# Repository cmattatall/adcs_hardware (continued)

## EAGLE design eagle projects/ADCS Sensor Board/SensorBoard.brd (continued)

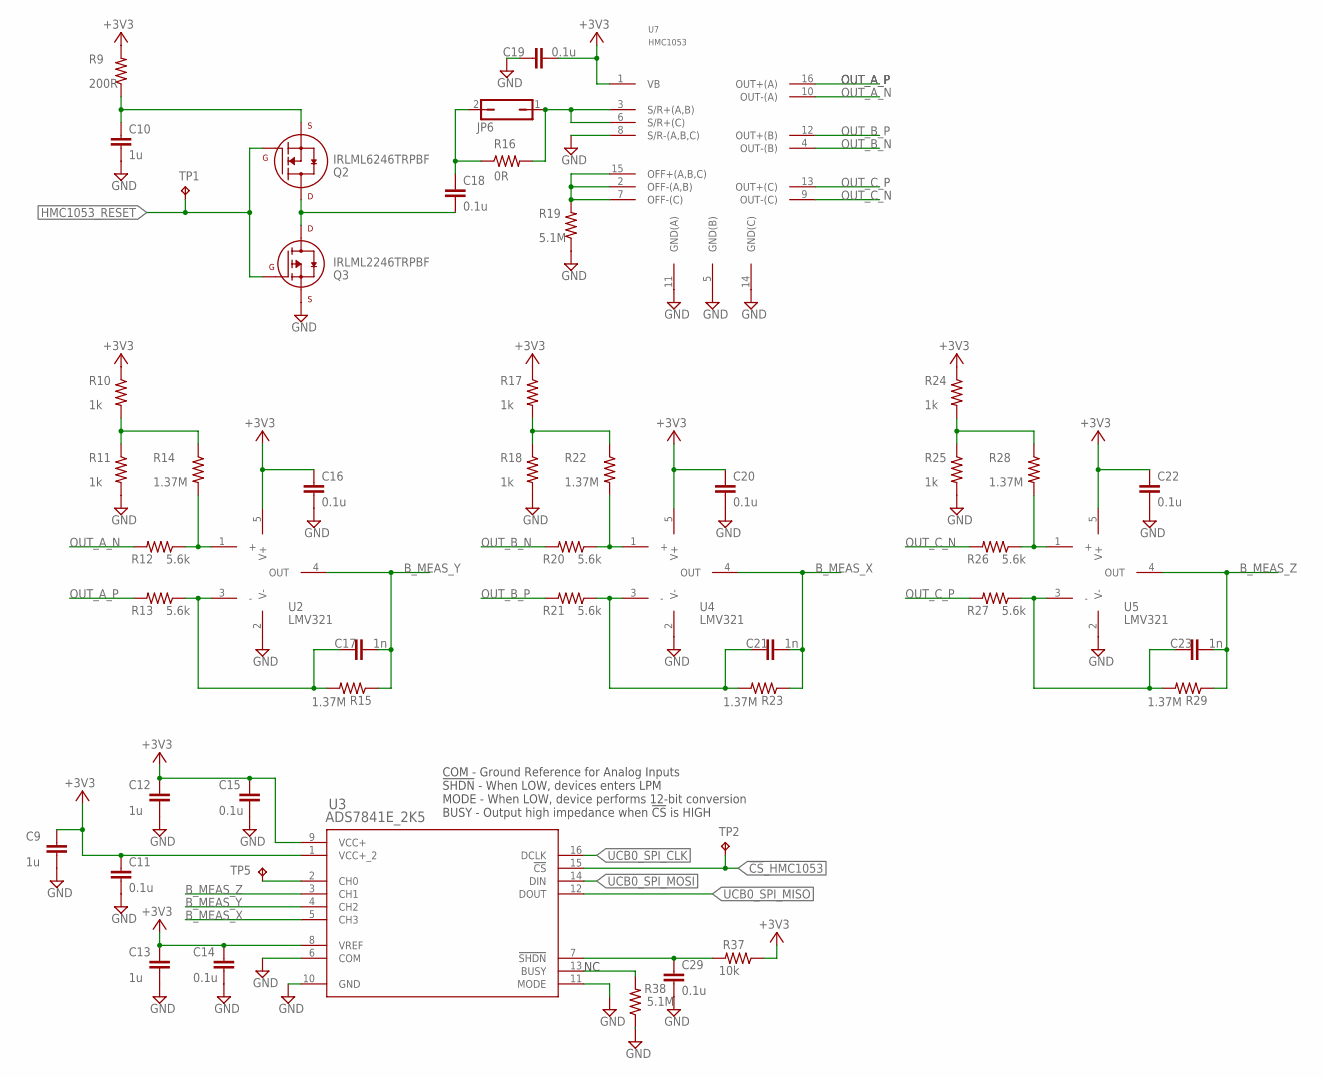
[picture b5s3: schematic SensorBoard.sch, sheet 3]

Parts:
C9, C12, C13: 1u; C0805
C10: 1u; C0603
C11, C14, C15, C16, C19, C20, C22, C29: 0.1u; C0603
C17, C21, C23: 1n; C0805
C18: 0.1u; C1206
JP6: JP1Q_; 1X02
Q2: IRLML6246TRPBF; SOT23-3P95_237X112L25X40N_MICRO3
Q3: IRLML2246TRPBF; SOT23-3P95_237X112L25X40N_MICRO3
R9: 200R; R0805
R10, R11, R17, R18, R24, R25: 1k; R0805
R12, R13, R20, R21, R26, R27: 5.6k; R0805
R14, R15, R22, R23, R28, R29: 1.37M; R0805
R16: 0R; R0805
R19: 5.1M; R0805
R37: 10k; R0805
R38: 5.1M; R0402
TP1, TP2, TP5: TESTPOINT; TP_P76H50
U2, U4, U5: LMV321; SC70-5P65_210X110L36X22N
U3: ADS7841E_2K5; DBQ16
U7: HMC1053; LCCS16P127_736X736X279L127X50N

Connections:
!CS!_HMC1053: TP2.1, U3.15 (!CS); also elsewhere on the board
+3V3: C9.1, C11.1, C12.1, C13.1, C14.1, C15.1, C16.1, C19.1, C20.1, C22.1, R9.2, R10.1, R17.1, R24.1, R37.1, U2.5 (V+), U3.1 (VCC+_2), U3.8 (VREF), U3.9 (VCC+), U4.5 (V+), U5.5 (V+), U7.1 (VB); also elsewhere on the board
B_MEAS_X: C21.2, R23.1, U3.5 (CH3), U4.4 (OUT)
B_MEAS_Y: C17.2, R15.1, U2.4 (OUT), U3.4 (CH2)
B_MEAS_Z: C23.2, R29.1, U3.3 (CH1), U5.4 (OUT)
GND: C9.2, C10.1, C11.2, C12.2, C13.2, C14.2, C15.2, C16.2, C19.2, C20.2, C22.2, C29.2, Q3.2 (S), R11.2, R18.2, R19.1, R25.2, R38.1, U2.2 (V-), U3.6 (COM), U3.10 (GND), U3.11 (MODE), U4.2 (V-), U5.2 (V-), U7.5 (GND(B)), U7.8 (S/R-(A,B,C)), U7.11 (GND(A)), U7.14 (GND(C)); also elsewhere on the board
HMC1053_RESET: Q2.1 (G), Q3.1 (G), TP1.1; also elsewhere on the board
unnamed: C18.1, Q2.3 (D), Q3.3 (D)
unnamed: R10.2, R11.1, R14.1
unnamed: C17.1, R13.1, R15.2, U2.3 (-)
unnamed: R12.1, R14.2, U2.1 (+)
unnamed: TP5.1, U3.2 (CH0)
unnamed: R38.2, U3.13 (BUSY)
unnamed: C29.1, R37.2, U3.7 (!SHDN)
unnamed: C18.2, JP6.2, R16.1
unnamed: R19.2, U7.2 (OFF-(A,B)), U7.7 (OFF-(C)), U7.15 (OFF+(A,B,C))
unnamed: JP6.1, R16.2, U7.3 (S/R+(A,B)), U7.6 (S/R+(C))
unnamed: C10.2, Q2.2 (S), R9.1
unnamed: R17.2, R18.1, R22.1
unnamed: C21.1, R21.1, R23.2, U4.3 (-)
unnamed: R20.1, R22.2, U4.1 (+)
unnamed: R24.2, R25.1, R28.1
unnamed: C23.1, R27.1, R29.2, U5.3 (-)
unnamed: R26.1, R28.2, U5.1 (+)
OUT_A_N: R12.2, U7.10 (OUT-(A))
OUT_A_P: R13.2, U7.16 (OUT+(A))
OUT_B_N: R20.2, U7.4 (OUT-(B))
OUT_B_P: R21.2, U7.12 (OUT+(B))
OUT_C_N: R26.2, U7.9 (OUT-(C))
OUT_C_P: R27.2, U7.13 (OUT+(C))
UCB0_SPI_CLK: U3.16 (DCLK); also elsewhere on the board
UCB0_SPI_MISO: U3.12 (DOUT); also elsewhere on the board
UCB0_SPI_MOSI: U3.14 (DIN); also elsewhere on the board

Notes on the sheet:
COM - Ground Reference for Analog Inputs !SHDN! - When LOW, devices enters LPM MODE - When LOW, device performs 12-bit conversion BUSY - Output high impedance when !CS! is HIGH

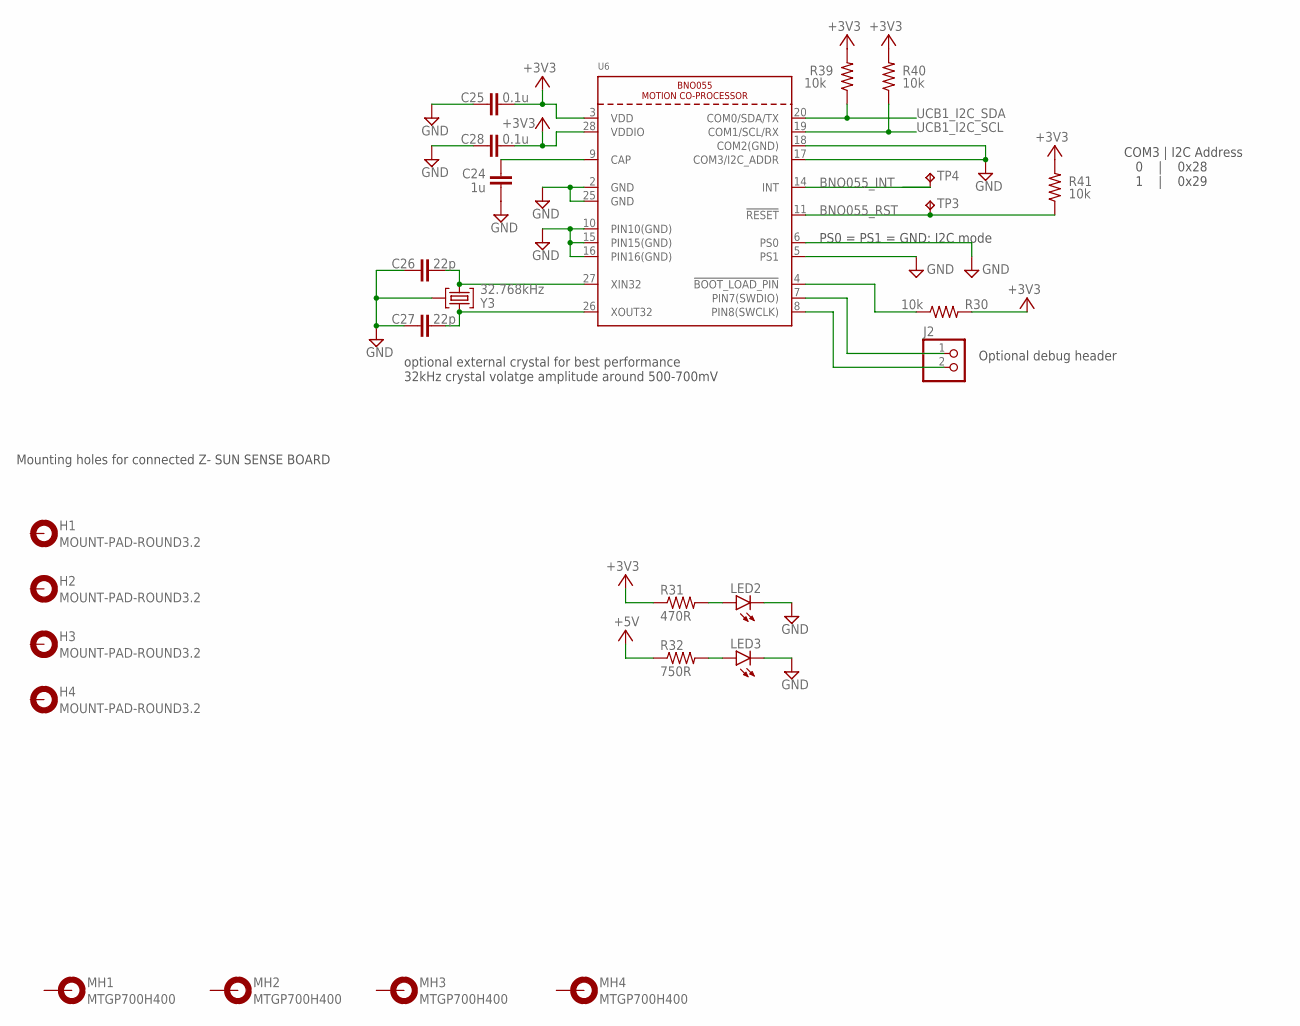
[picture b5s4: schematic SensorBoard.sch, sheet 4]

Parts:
C24: 1u; C0402
C25, C28: 0.1u; C0402
C26, C27: 22p; C0402
H1, H2, H3, H4: MOUNT-PAD-ROUND3.2; 3,2-PAD
J2: HDR_1X2_; 1X02
LED2, LED3: LEDCHIP-LED0603; CHIP-LED0603
MH1, MH2, MH3, MH4: MTGP700H400
R30, R39, R40, R41: 10k; R0402
R31: 470R; R0603
R32: 750R; R0603
TP3, TP4: TESTPOINT; TP_P76H50
U6: BNO055
Y3: 32.768kHz; MS3V-T1R

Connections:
+3V3: C25.2, C28.2, R30.2, R31.1, R39.2, R40.2, R41.2, U6.3 (VDD), U6.28 (VDDIO); also elsewhere on the board
+5V: R32.1; also elsewhere on the board
BNO055_INT: TP4.1, U6.14 (INT)
BNO055_RST: R41.1, TP3.1, U6.11 (!RESET)
GND: C24.1, C25.1, C26.1, C27.1, C28.1, LED2.C, LED3.C, U6.2 (GND), U6.5 (PS1), U6.6 (PS0), U6.10 (PIN10(GND)), U6.15 (PIN15(GND)), U6.16 (PIN16(GND)), U6.17 (COM3/I2C_ADDR), U6.18 (COM2(GND)), U6.25 (GND), Y3.P3 (GND); also elsewhere on the board
unnamed: LED2.A, R31.2
unnamed: LED3.A, R32.2
unnamed: R30.1, U6.4 (!BOOT_LOAD_PIN)
unnamed: C24.2, U6.9 (CAP)
unnamed: C26.2, U6.27 (XIN32), Y3.P1 (1)
unnamed: C27.2, U6.26 (XOUT32), Y3.P2 (2)
unnamed: J2.1, U6.7 (PIN7(SWDIO))
unnamed: J2.2, U6.8 (PIN8(SWCLK))
UCB1_I2C_SCL: R40.1, U6.19 (COM1/SCL/RX); also elsewhere on the board
UCB1_I2C_SDA: R39.1, U6.20 (COM0/SDA/TX); also elsewhere on the board

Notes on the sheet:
optional external crystal for best performance 32kHz crystal volatge amplitude around 500-700mV
Optional debug header
PS0 = PS1 = GND: I2C mode
COM3 | I2C Address 0 | 0x28 1 | 0x29
Mounting holes for connected Z- SUN SENSE BOARD

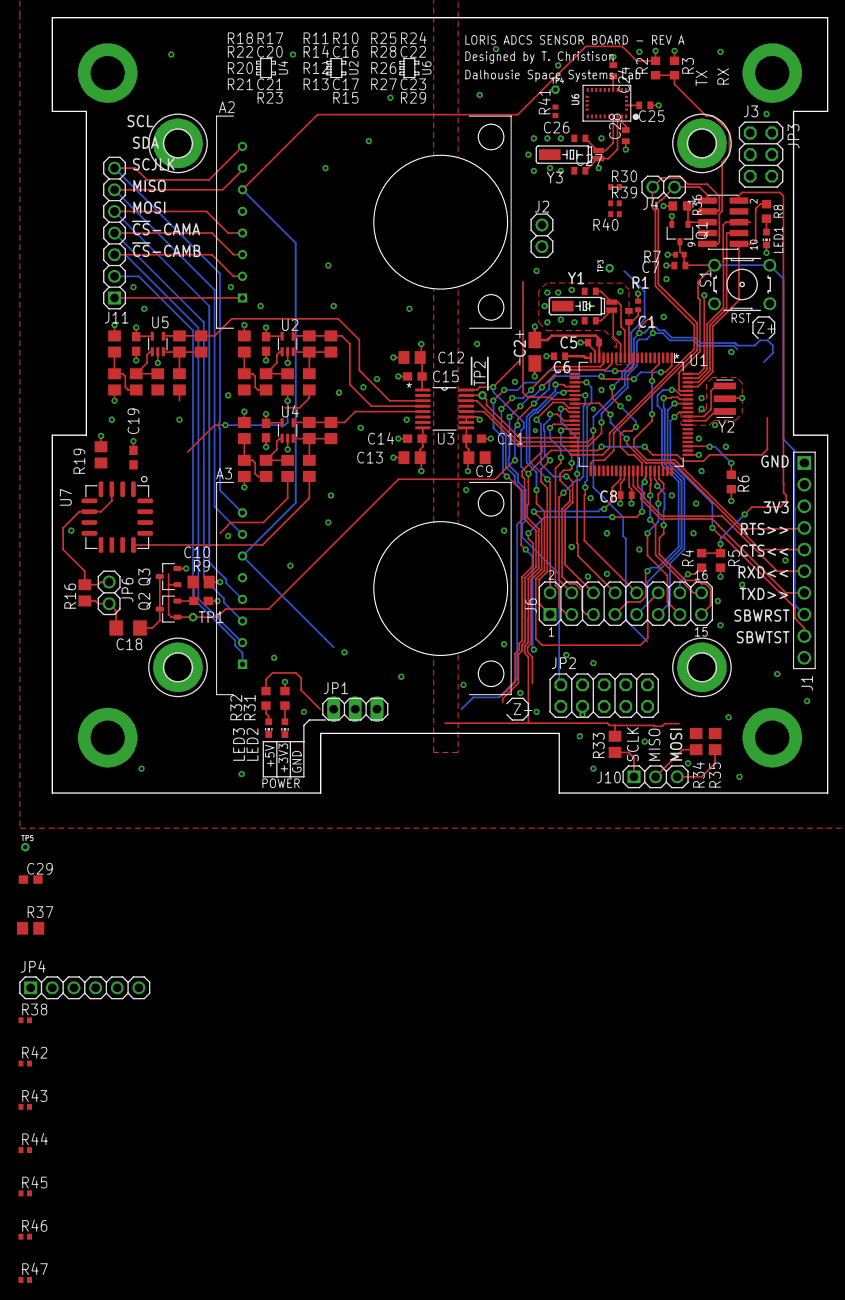
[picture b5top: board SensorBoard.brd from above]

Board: 4 copper layers, 91.0 x 91.0 mm, 120 parts (0 on the bottom side), 107 nets.

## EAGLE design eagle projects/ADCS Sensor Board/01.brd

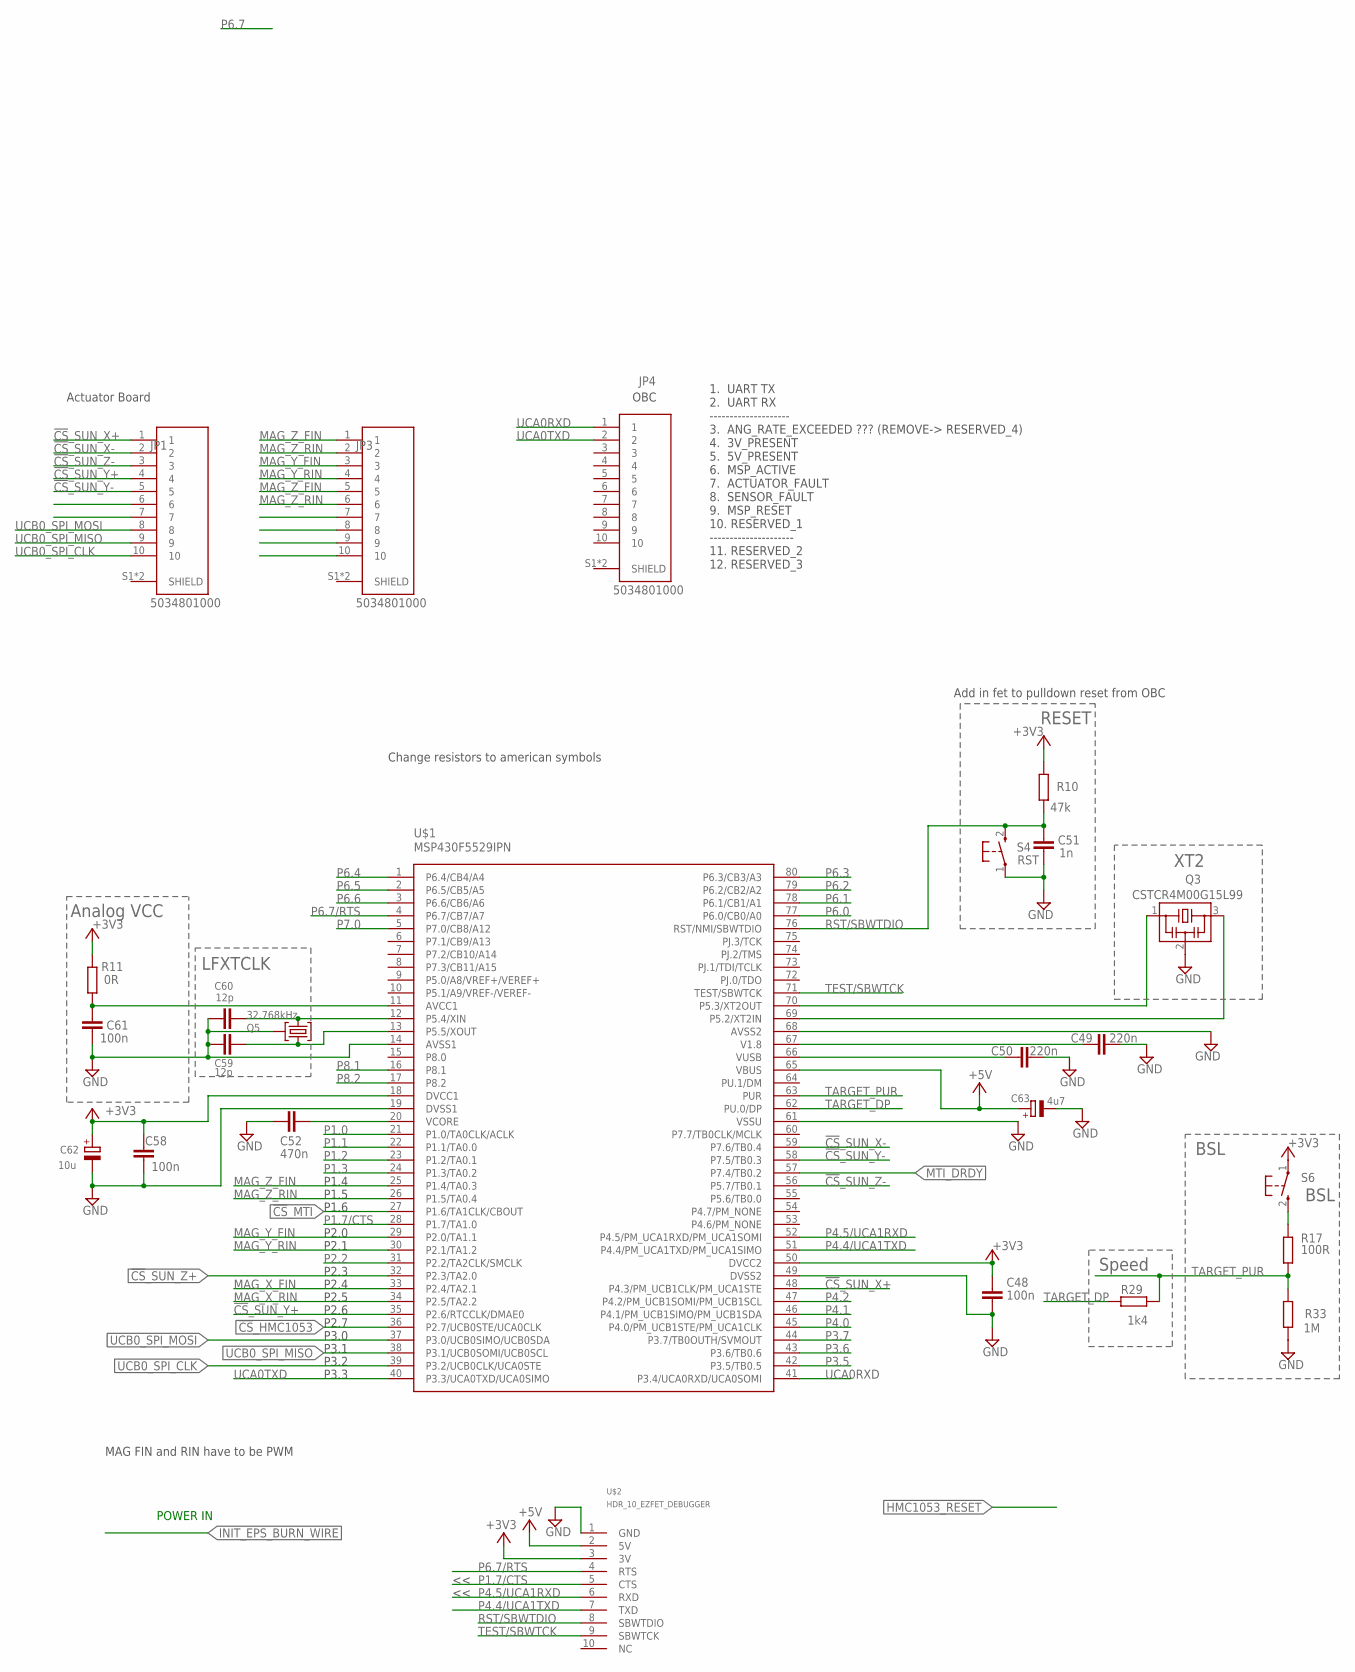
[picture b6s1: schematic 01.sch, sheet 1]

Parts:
C48, C58, C61: 100n; 0402
C49, C50: 220n; 0402
C51: 1n; 0402
C52: 470n; 0402
C59, C60: 12p; 0402
C62: 10u; A/3216-18R
C63: 4u7; A/3216-18R
JP1, JP3, JP4: 5034801000; MOLEX_5034801000
Q3: CSTCR4M00G15L99; MURATA-FILTER_CSTCR
Q5: 32.768kHz; MS3V-T1R
R10: 47k; 0402
R11: 0R; 0402
R17: 100R; 0402
R29: 1k4; 0402
R33: 1M; 0402
S4: RST; PBTH
S6: BSL; PBTH
U$1: MSP430F5529IPN; QFP80P50_1400X1400X160L60X22N
U$2: HDR_10_EZFET_DEBUGGER; HDRV10W66P254_10X1_2540X254H858

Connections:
!CS!_HMC1053: U$1.36 (P2.7/UCB0STE/UCA0CLK); also elsewhere on the board
!CS!_MTI: U$1.27 (P1.6/TA1CLK/CBOUT)
!CS!_SUN_X+: JP1.1, U$1.48 (P4.3/PM_UCB1CLK/PM_UCA1STE)
!CS!_SUN_X-: JP1.2, U$1.59 (P7.6/TB0.4)
!CS!_SUN_Y+: JP1.4, U$1.35 (P2.6/RTCCLK/DMAE0)
!CS!_SUN_Y-: JP1.5, U$1.58 (P7.5/TB0.3)
!CS!_SUN_Z+: U$1.32 (P2.3/TA2.0)
!CS!_SUN_Z-: JP1.3, U$1.56 (P5.7/TB0.1); also elsewhere on the board
+3V3: C48.1, C58.2, C62.+, R10.2, R11.2, S6.1, U$1.18 (DVCC1), U$1.50 (DVCC2), U$2.3 (3V); also elsewhere on the board
+5V: C63.+, U$1.65 (VBUS), U$2.2 (5V); also elsewhere on the board
AVCC1: C61.1, R11.1, U$1.11 (AVCC1)
GND: C48.2, C49.2, C50.2, C51.2, C52.1, C58.1, C59.1, C60.1, C61.2, C62.-, C63.-, Q3.2, Q5.P3 (GND), R33.1, S4.1, U$1.14 (AVSS1), U$1.19 (DVSS1), U$1.49 (DVSS2), U$1.61 (VSSU), U$1.68 (AVSS2), U$2.1 (GND); also elsewhere on the board
MAG_X_FIN: U$1.33 (P2.4/TA2.1)
MAG_X_RIN: U$1.34 (P2.5/TA2.2)
MAG_Y_FIN: JP3.3, U$1.29 (P2.0/TA1.1)
MAG_Y_RIN: JP3.4, U$1.30 (P2.1/TA1.2)
MAG_Z_FIN: JP3.1, JP3.5, U$1.25 (P1.4/TA0.3)
MAG_Z_RIN: JP3.2, JP3.6, U$1.26 (P1.5/TA0.4)
MTI_DRDY: U$1.57 (P7.4/TB0.2); also elsewhere on the board
unnamed: R17.1, S6.2 (S)
P1.0: U$1.21 (P1.0/TA0CLK/ACLK)
P1.1: U$1.22 (P1.1/TA0.0)
P1.2: U$1.23 (P1.2/TA0.1)
P1.3: U$1.24 (P1.3/TA0.2)
P1.7/CTS: U$1.28 (P1.7/TA1.0), U$2.5 (CTS)
P2.2: U$1.31 (P2.2/TA2CLK/SMCLK)
P3.5: U$1.42 (P3.5/TB0.5)
P3.6: U$1.43 (P3.6/TB0.6)
P3.7: U$1.44 (P3.7/TB0OUTH/SVMOUT)
P4.0: U$1.45 (P4.0/PM_UCB1STE/PM_UCA1CLK)
P4.1: U$1.46 (P4.1/PM_UCB1SIMO/PM_UCB1SDA)
P4.2: U$1.47 (P4.2/PM_UCB1SOMI/PM_UCB1SCL)
P4.4/UCA1TXD: U$1.51 (P4.4/PM_UCA1TXD/PM_UCA1SIMO), U$2.7 (TXD)
P4.5/UCA1RXD: U$1.52 (P4.5/PM_UCA1RXD/PM_UCA1SOMI), U$2.6 (RXD)
P5.2/XT2IN1: Q3.3, U$1.69 (P5.2/XT2IN)
P5.3/XT2OUT1: Q3.1, U$1.70 (P5.3/XT2OUT)
P5.4/XIN1: C60.2, Q5.P2 (2), U$1.12 (P5.4/XIN)
P5.5/XOUT1: C59.2, Q5.P1 (1), U$1.13 (P5.5/XOUT)
P6.0: U$1.77 (P6.0/CB0/A0)
P6.1: U$1.78 (P6.1/CB1/A1)
P6.2: U$1.79 (P6.2/CB2/A2)
P6.3: U$1.80 (P6.3/CB3/A3)
P6.4: U$1.1 (P6.4/CB4/A4)
P6.5: U$1.2 (P6.5/CB5/A5)
P6.6: U$1.3 (P6.6/CB6/A6)
P6.7/RTS: U$1.4 (P6.7/CB7/A7), U$2.4 (RTS)
P7.0: U$1.5 (P7.0/CB8/A12)
P8.1: U$1.16 (P8.1)
P8.2: U$1.17 (P8.2)
RST/SBWTDIO: C51.1, R10.1, S4.2 (S), U$1.76 (RST/NMI/SBWTDIO), U$2.8 (SBWTDIO)
TARGET_DP: R29.2, U$1.62 (PU.0/DP)
TARGET_PUR: R17.2, R29.1, R33.2, U$1.63 (PUR)
TARGET_VUSB1: C50.1, U$1.66 (VUSB)
TEST/SBWTCK: U$1.71 (TEST/SBWTCK), U$2.9 (SBWTCK)
UCA0RXD: JP4.1, U$1.41 (P3.4/UCA0RXD/UCA0SOMI)
UCA0TXD: JP4.2, U$1.40 (P3.3/UCA0TXD/UCA0SIMO)
UCB0_SPI_CLK: JP1.10, U$1.39 (P3.2/UCB0CLK/UCA0STE); also elsewhere on the board
UCB0_SPI_MISO: JP1.9, U$1.38 (P3.1/UCB0SOMI/UCB0SCL); also elsewhere on the board
UCB0_SPI_MOSI: JP1.8, U$1.37 (P3.0/UCB0SIMO/UCB0SDA); also elsewhere on the board
V1: C49.1, U$1.67 (V1.8)
VCORE1: C52.2, U$1.20 (VCORE)

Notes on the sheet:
Add in fet to pulldown reset from OBC
RESET
LFXTCLK
XT2
BSL
Speed
Analog VCC
P3.3
P3.2
P3.1
P3.0
P2.7
P2.6
P2.5
P2.4
P2.3
P2.1
P2.0
P1.6
P1.5
P1.4
MAG FIN and RIN have to be PWM
Actuator Board
OBC
1. UART TX 2. UART RX -------------------- 3. ANG_RATE_EXCEEDED ??? (REMOVE-> RESERVED_4) 4. 3V_PRESENT 5. 5V_PRESENT 6. MSP_ACTIVE 7. ACTUATOR_FAULT 8. SENSOR_FAULT 9. MSP_RESET 10. RESERVED_1 --------------------- 11. RESERVED_2 12. RESERVED_3
Change resistors to american symbols
POWER IN

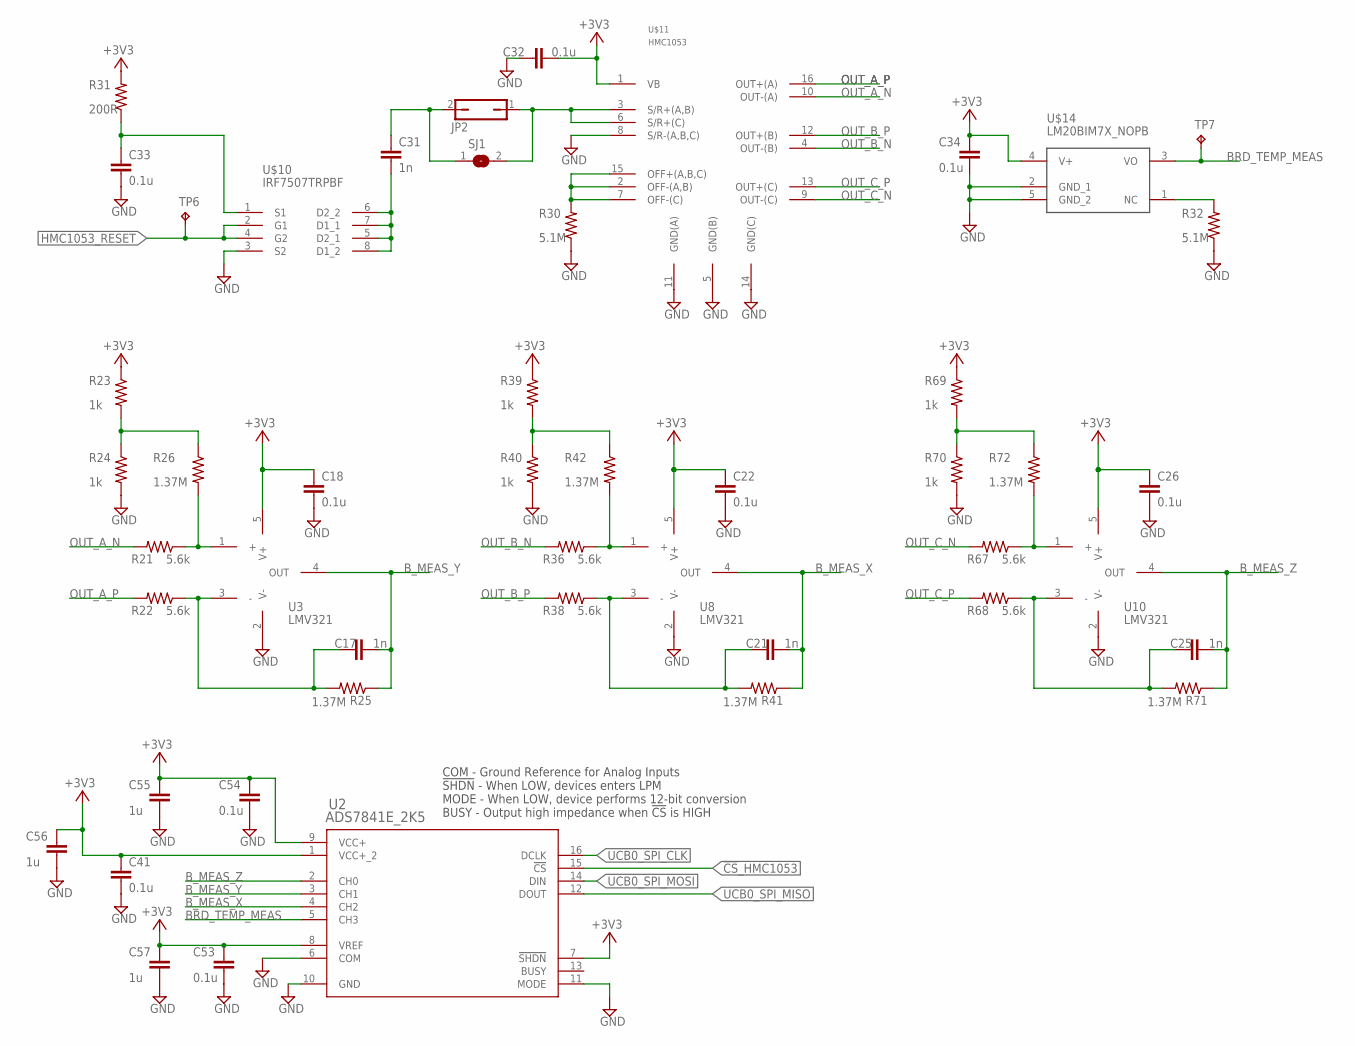
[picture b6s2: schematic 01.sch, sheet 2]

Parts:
C17, C21, C25: 1n; C0805
C18, C22, C26, C32, C33, C34, C41, C53, C54: 0.1u; C0603
C31: 1n; C1206
C55, C56, C57: 1u; C1206
JP2: JP1Q; JP1
R21, R22, R36, R38, R67, R68: 5.6k; R0805
R23, R24, R39, R40, R69, R70: 1k; R0805
R25, R26, R41, R42, R71, R72: 1.37M; R0805
R30, R32: 5.1M; R1206
R31: 200R; R1206
SJ1: SJ
TP6: TPPAD1-13; P1-13
TP7: TPB1,27; B1,27
U2: ADS7841E_2K5; DBQ16
U3, U8, U10: LMV321; SOT23-5P65_210X110L36X22N
U$10: IRF7507TRPBF; SOP8P65_300X490X111L53X30N
U$11: HMC1053; LCCS16P127_736X736X279L127X50N
U$14: LM20BIM7X_NOPB; SOT23-5P65_210X110L40X22N_LM20

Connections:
!CS!_HMC1053: U2.15 (!CS); also elsewhere on the board
+3V3: C18.1, C22.1, C26.1, C32.1, C34.2, C41.1, C53.1, C54.1, C55.1, C56.1, C57.1, R23.1, R31.2, R39.1, R69.1, U2.1 (VCC+_2), U2.7 (!SHDN), U2.8 (VREF), U2.9 (VCC+), U3.5 (V+), U8.5 (V+), U10.5 (V+), U$11.1 (VB), U$14.4 (V+); also elsewhere on the board
BRD_TEMP_MEAS: TP7.TP, U2.5 (CH3), U$14.3 (VO)
B_MEAS_X: C21.2, R41.1, U2.4 (CH2), U8.4 (OUT)
B_MEAS_Y: C17.2, R25.1, U2.3 (CH1), U3.4 (OUT)
B_MEAS_Z: C25.2, R71.1, U2.2 (CH0), U10.4 (OUT)
GND: C18.2, C22.2, C26.2, C32.2, C33.1, C34.1, C41.2, C53.2, C54.2, C55.2, C56.2, C57.2, R24.2, R30.1, R32.1, R40.2, R70.2, U2.6 (COM), U2.10 (GND), U2.11 (MODE), U3.2 (V-), U8.2 (V-), U10.2 (V-), U$10.3 (S2), U$11.5 (GND(B)), U$11.8 (S/R-(A,B,C)), U$11.11 (GND(A)), U$11.14 (GND(C)), U$14.2 (GND_1), U$14.5 (GND_2); also elsewhere on the board
HMC1053_RESET: TP6.TP, U$10.2 (G1), U$10.4 (G2)
unnamed: R23.2, R24.1, R26.1
unnamed: C17.1, R22.1, R25.2, U3.3 (-)
unnamed: R21.1, R26.2, U3.1 (+)
unnamed: C31.2, JP2.2, SJ1.1
unnamed: R30.2, U$11.2 (OFF-(A,B)), U$11.7 (OFF-(C)), U$11.15 (OFF+(A,B,C))
unnamed: JP2.1, SJ1.2, U$11.3 (S/R+(A,B)), U$11.6 (S/R+(C))
unnamed: C31.1, U$10.5 (D2_1), U$10.6 (D2_2), U$10.7 (D1_1), U$10.8 (D1_2)
unnamed: C33.2, R31.1, U$10.1 (S1)
unnamed: R32.2, U$14.1 (NC)
unnamed: R39.2, R40.1, R42.1
unnamed: C21.1, R38.1, R41.2, U8.3 (-)
unnamed: R36.1, R42.2, U8.1 (+)
unnamed: R69.2, R70.1, R72.1
unnamed: C25.1, R68.1, R71.2, U10.3 (-)
unnamed: R67.1, R72.2, U10.1 (+)
OUT_A_N: R21.2, U$11.10 (OUT-(A))
OUT_A_P: R22.2, U$11.16 (OUT+(A))
OUT_B_N: R36.2, U$11.4 (OUT-(B))
OUT_B_P: R38.2, U$11.12 (OUT+(B))
OUT_C_N: R67.2, U$11.9 (OUT-(C))
OUT_C_P: R68.2, U$11.13 (OUT+(C))
UCB0_SPI_CLK: U2.16 (DCLK); also elsewhere on the board
UCB0_SPI_MISO: U2.12 (DOUT); also elsewhere on the board
UCB0_SPI_MOSI: U2.14 (DIN); also elsewhere on the board

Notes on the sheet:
COM - Ground Reference for Analog Inputs !SHDN! - When LOW, devices enters LPM MODE - When LOW, device performs 12-bit conversion BUSY - Output high impedance when !CS! is HIGH

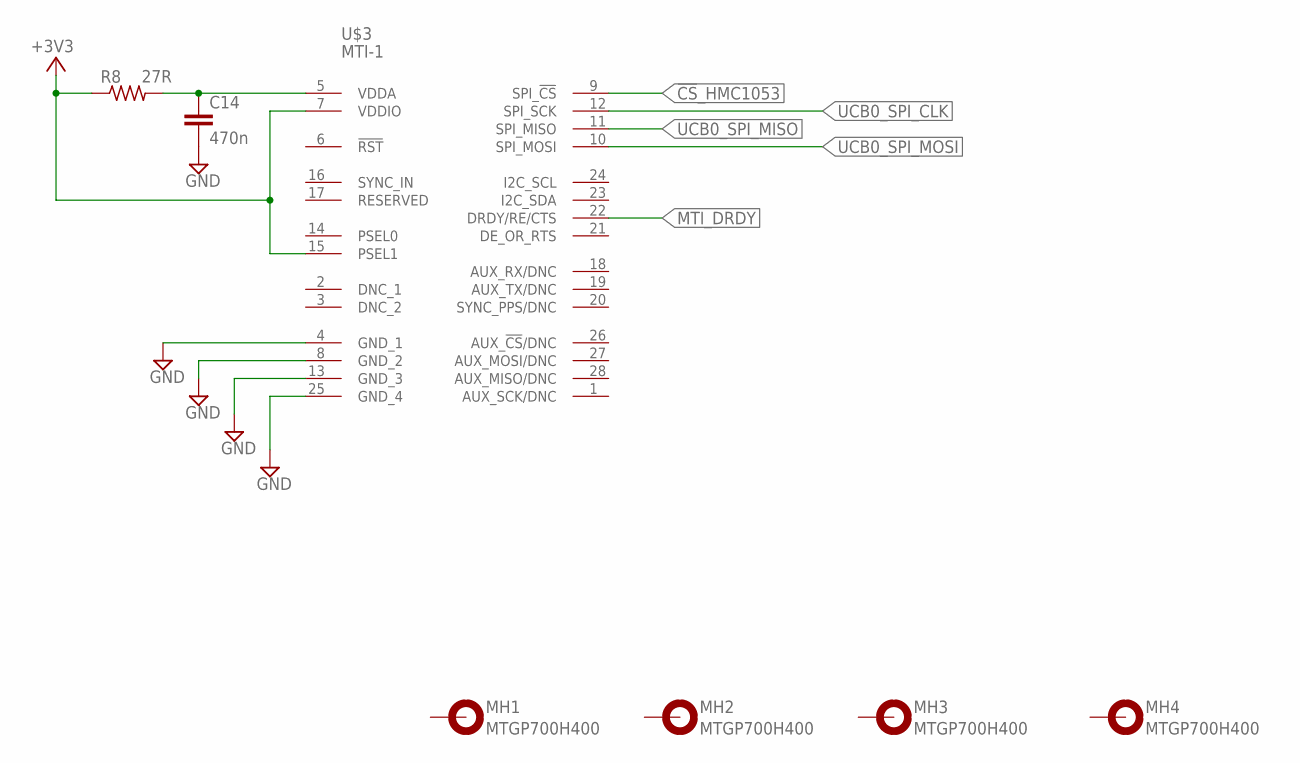
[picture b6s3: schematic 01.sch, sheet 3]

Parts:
C14: 470n; C0805
MH1, MH2, MH3, MH4: MTGP700H400
R8: 27R; R0805
U$3: MTI-1; LCC28P127_1210X1210X260L90X63_MTI-1

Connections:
!CS!_HMC1053: U$3.9 (SPI_!CS); also elsewhere on the board
+3V3: R8.1, U$3.7 (VDDIO), U$3.15 (PSEL1); also elsewhere on the board
GND: C14.1, U$3.4 (GND_1), U$3.8 (GND_2), U$3.13 (GND_3), U$3.25 (GND_4); also elsewhere on the board
MTI_DRDY: U$3.22 (DRDY/RE/CTS); also elsewhere on the board
unnamed: C14.2, R8.2, U$3.5 (VDDA)
UCB0_SPI_CLK: U$3.12 (SPI_SCK); also elsewhere on the board
UCB0_SPI_MISO: U$3.11 (SPI_MISO); also elsewhere on the board
UCB0_SPI_MOSI: U$3.10 (SPI_MOSI); also elsewhere on the board

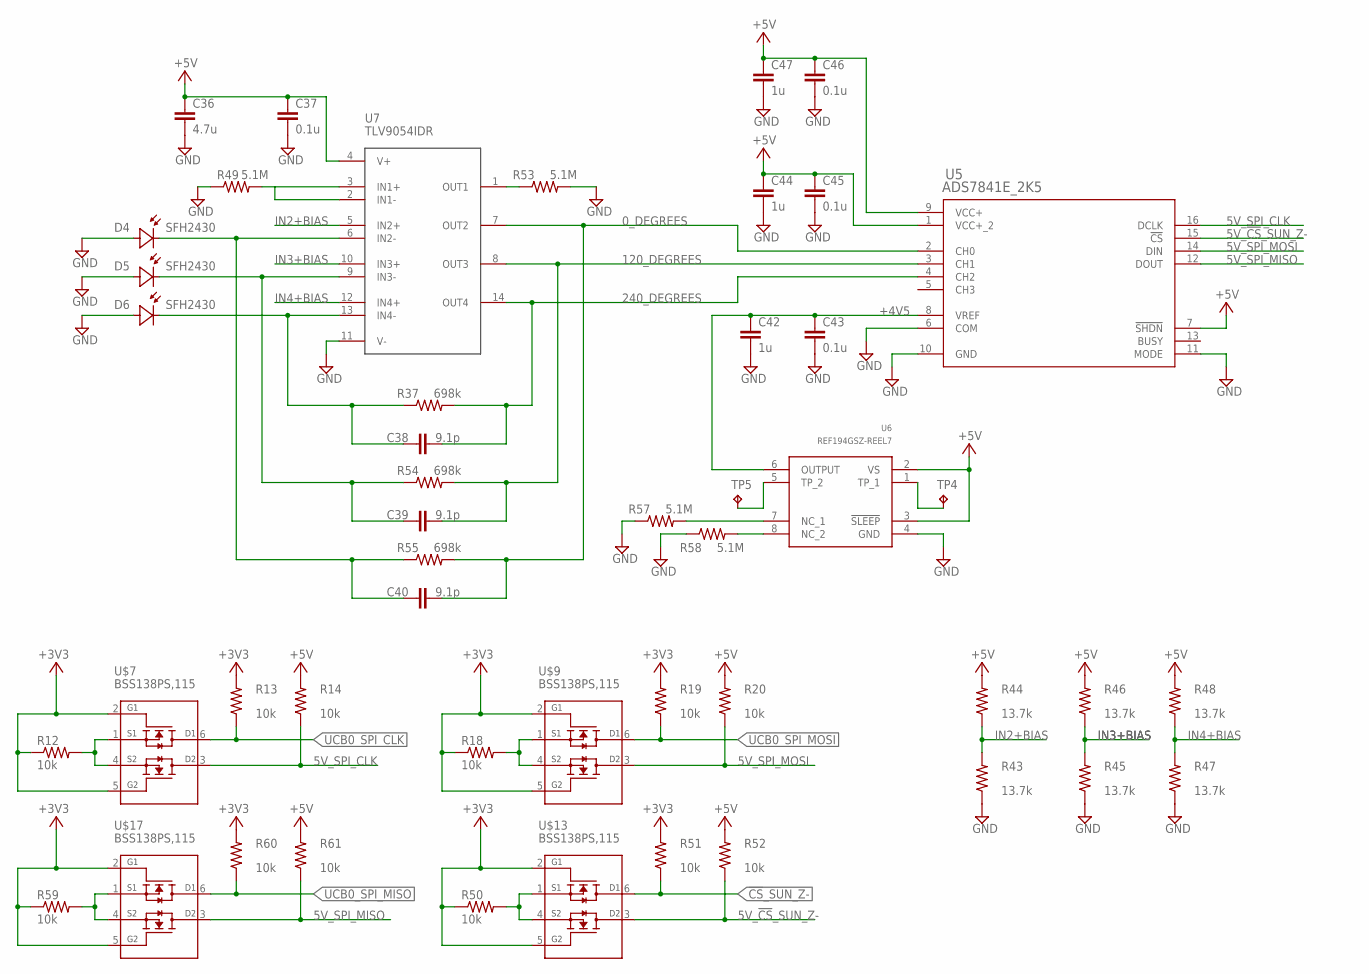
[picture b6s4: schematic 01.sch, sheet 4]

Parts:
C36: 4.7u; C0603
C37, C43, C45, C46: 0.1u; C0603
C38, C39, C40: 9.1p; C0603
C42, C44, C47: 1u; C0603
D4, D5, D6: SFH2430; JP1Y_LED_SCREEN
R12, R13, R14, R18, R19, R20, R50, R51, R52, R59, R60, R61: 10k; R0402
R37, R54, R55: 698k; R0603
R43, R44, R45, R46, R47, R48: 13.7k; R0603
R49, R53, R57, R58: 5.1M; R0603
TP4, TP5: TPB1,27; B1,27
U5: ADS7841E_2K5; DBQ16
U6: REF194GSZ-REEL7; SOIC8P127_490X600X175L83X41N_REF194GSZ-REEL7
U7: TLV9054IDR; SOIC14P127_865X600X175L83X41N_TLV9054IDR
U$7, U$9, U$13, U$17: BSS138PS,115; SOT23-6P65_200X110L30X25N_BSS138PS,115

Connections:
0_DEGREES: C40.2, R55.2, U5.2 (CH0), U7.7 (OUT2)
5V_!CS!_SUN_Z-: R52.1, U5.15 (!CS), U$13.3 (D2)
5V_SPI_CLK: R14.1, U5.16 (DCLK), U$7.3 (D2)
5V_SPI_MISO: R61.1, U5.12 (DOUT), U$17.3 (D2)
5V_SPI_MOSI: R20.1, U5.14 (DIN), U$9.3 (D2)
120_DEGREES: C39.2, R54.2, U5.3 (CH1), U7.8 (OUT3)
240_DEGREES: C38.2, R37.2, U5.4 (CH2), U7.14 (OUT4)
!CS!_SUN_Z-: R51.1, U$13.6 (D1); also elsewhere on the board
+3V3: R12.1, R13.2, R18.1, R19.2, R50.1, R51.2, R59.1, R60.2, U$7.2 (G1), U$7.5 (G2), U$9.2 (G1), U$9.5 (G2), U$13.2 (G1), U$13.5 (G2), U$17.2 (G1), U$17.5 (G2); also elsewhere on the board
+4V5: C42.1, C43.1, U5.8 (VREF), U6.6 (OUTPUT)
+5V: C36.1, C37.1, C44.1, C45.1, C46.1, C47.1, R14.2, R20.2, R44.2, R46.2, R48.2, R52.2, R61.2, U5.1 (VCC+_2), U5.7 (!SHDN), U5.9 (VCC+), U6.2 (VS), U6.3 (!SLEEP), U7.4 (V+); also elsewhere on the board
GND: C36.2, C37.2, C42.2, C43.2, C44.2, C45.2, C46.2, C47.2, D4.2 (A), D5.2 (A), D6.2 (A), R43.1, R45.1, R47.1, R49.1, R53.2, R57.1, R58.1, U5.6 (COM), U5.10 (GND), U5.11 (MODE), U6.4 (GND), U7.11 (V-); also elsewhere on the board
IN2+BIAS: R43.2, R44.1, U7.5 (IN2+)
IN3+BIAS: R45.2, R46.1, U7.10 (IN3+)
IN4+BIAS: R47.2, R48.1, U7.12 (IN4+)
unnamed: R12.2, U$7.1 (S1), U$7.4 (S2)
unnamed: R49.2, U7.2 (IN1-), U7.3 (IN1+)
unnamed: R53.1, U7.1 (OUT1)
unnamed: C38.1, D6.1 (C), R37.1, U7.13 (IN4-)
unnamed: R18.2, U$9.1 (S1), U$9.4 (S2)
unnamed: C39.1, D5.1 (C), R54.1, U7.9 (IN3-)
unnamed: C40.1, D4.1 (C), R55.1, U7.6 (IN2-)
unnamed: TP5.TP, U6.5 (TP_2)
unnamed: TP4.TP, U6.1 (TP_1)
unnamed: R57.2, U6.7 (NC_1)
unnamed: R50.2, U$13.1 (S1), U$13.4 (S2)
unnamed: R58.2, U6.8 (NC_2)
unnamed: R59.2, U$17.1 (S1), U$17.4 (S2)
UCB0_SPI_CLK: R13.1, U$7.6 (D1); also elsewhere on the board
UCB0_SPI_MISO: R60.1, U$17.6 (D1); also elsewhere on the board
UCB0_SPI_MOSI: R19.1, U$9.6 (D1); also elsewhere on the board

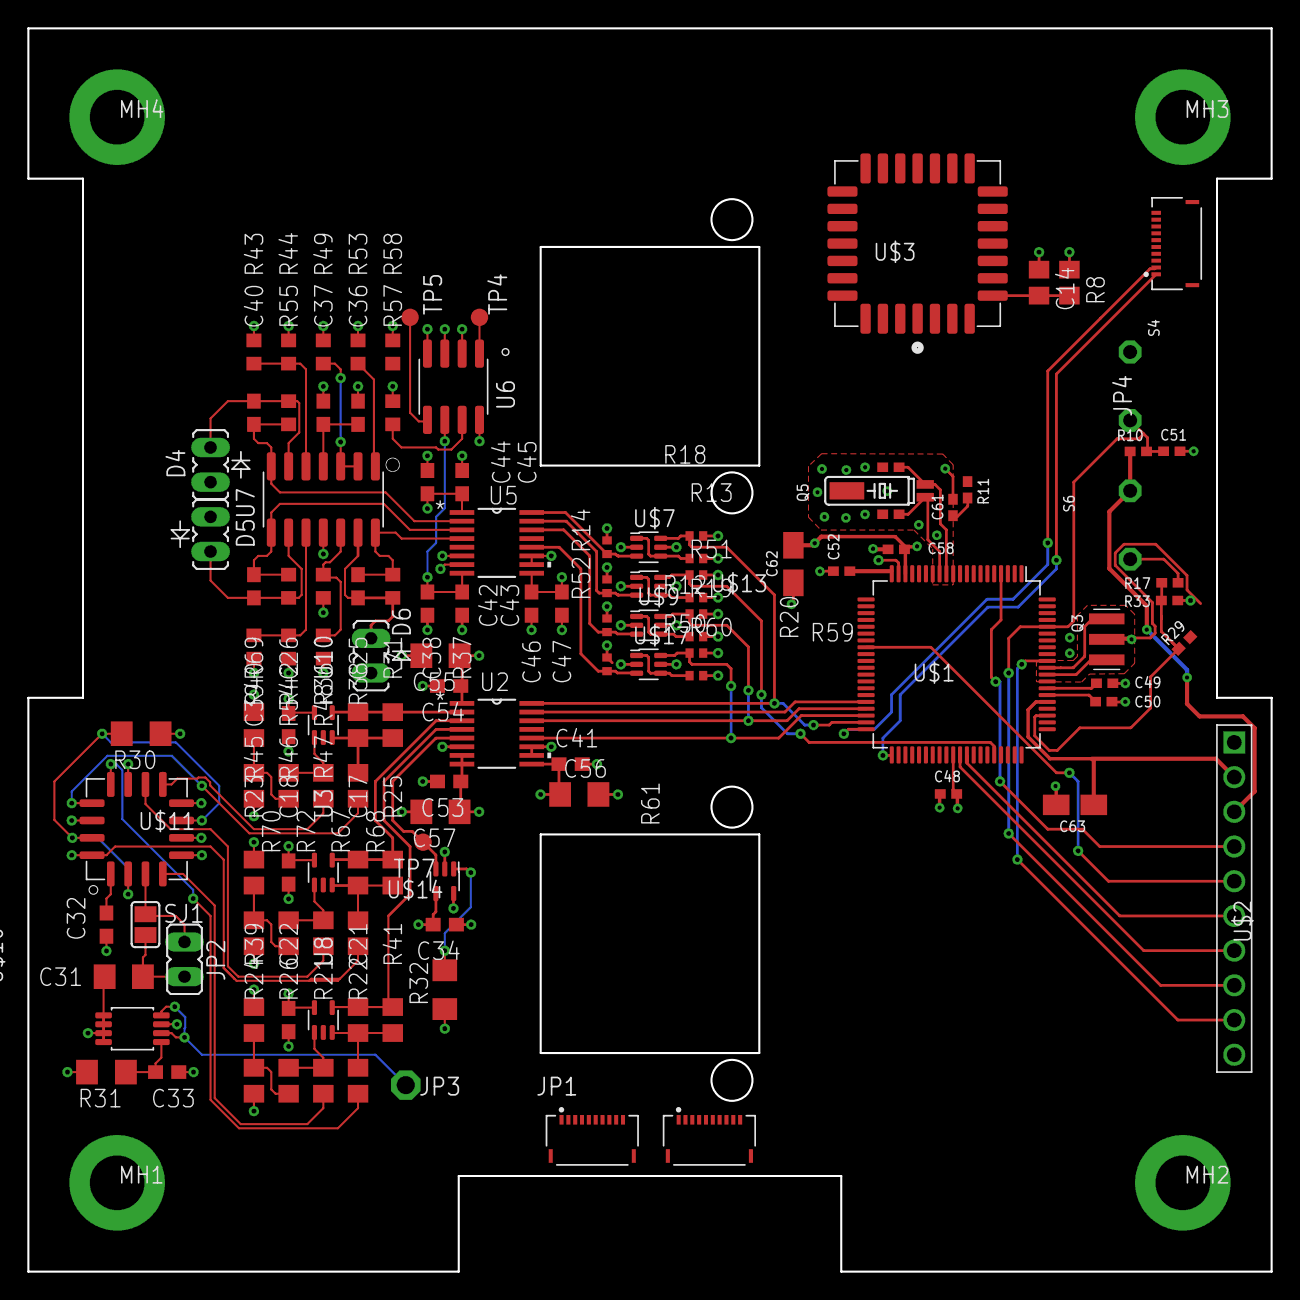
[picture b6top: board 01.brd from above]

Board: 2 copper layers, 91.0 x 91.0 mm, 128 parts (1 on the bottom side), 87 nets.

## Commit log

2020-09-28 added project structure and readmes to the directories
2020-09-28 Update README.md
    Add description to the version control process for the hardware repo in readme
2020-10-05 Uploading eagle projects for actuator board and sensor board
    Also added eagle relevant information to main readme
2020-10-05 added .brd and .sch backup files to .gitignore
2020-10-05 added embedded link for system block diagram image to readme
2020-10-05 readme formatting
2020-10-05 Renamed sensor board files. Added notes to schematic for remaining work
2020-10-19 Buncha layout done
2020-10-22 Board update commit before removing Z+ sunsensor from layout
2020-10-26 Added files for Sunsensor Boards
2020-10-26 Updated placeholder footprints on actuator boards
    Added photodiode amplifier circuitry for X+/- and Y+/- faces
2020-10-27 Added magnetorquer driving circuitry
2020-10-27 Moved reaction wheels to its own pages
2020-10-28 Added speed counter circuitry (p3) and h-bridge logic table (p1)
2020-10-28 add current sensing circuitry to sheet 7
2020-10-28 Added pinout and logic level shifting to speed counting circuitry
2020-10-29 updated system diagram
2020-10-29 updated diagram in readme
2020-10-29 add new frames
2020-10-29 Added connector pins
2020-10-29 removed unused usb stuff from msp430
2020-10-29 Finished up pinout connectors on sensor board
2020-10-30 Laid out pinout traces
2020-10-30 Added cutouts to ground plane to separarte analog and digital
2020-11-03 Added copper pours to top and bottom. Fixed silksreens, smoothed traces
2020-11-05 Added spi bus test headers
2020-11-07 added indicator LEDs, drill legend, and adjusted board thickness
2020-11-07 Updated traces/ vias to meet manufacturer DRC
2020-11-07 Removed temperature sensor
2020-11-07 Added testpoints, updated drill chart
    Added missing MTI-1 IMU reset signal to msp430
2020-11-07 Fixed testpoint silkscreens, moved vias where silk interfered
2020-11-07 Renumbered parts and exported bom CSV
2020-11-09 Replaced obsolete transistor Q2
2020-11-12 added motor controller
2020-11-14 Rev A Final-- I think
2020-11-19 Added releases. A.1 includes missing completed BOM
2020-11-19 Adding Pick and place files
2020-11-19 Adding exported bom and updated gitignore
2020-11-19 Updated gitignore
2020-11-19 updated all libraries
2020-12-04 Added REV A Schematic PDF
2020-12-20 Updated logic level shifter mosfet packages and board dimensions
2020-12-21 epf file autoupdate
2020-12-21 Updated motor speed circuitry to smd versions
2020-12-21 Added Demultiplexer
2020-12-21 Replaced logic level shift circuitry with simpler versions
2020-12-22 updated schematic for proper wave cmp config and attached motors
2020-12-30 Added magnetorquer and reaction wheel footprints
2021-01-04 Updated board pinout to sensor board and pinout reformated first two pages for readability
2021-01-04 made changes to motor driver and added new page with new motor drivers
2021-01-05 added new motor drivers
2021-01-05 revise current sensing circuitry for magnetorquers
2021-01-05 add initial implementation circuit of ADC for current sensing. Add shunt resistor value for current sensing comparator
2021-01-06 Change shunt resistor value from 1R->5R on current sensing circuits for MQTR
2021-01-08 removed old motor drivers and named current sens pins
2021-01-08 added current sense circuitry and ADC
2021-01-12 Preliminary changes to board layout
2021-01-12 Update DR10970V motor driver IC footprint and symbol
2021-01-12 Made moules of motor drivers for layout
2021-01-12 Update mqtr circuit
2021-01-12 Remove unneeded silk from TPs
2021-01-13 Add ground plane pour and change board stackup to 4 layers
2021-01-13 Change silk font to vector style. Reduce size. Remove silkscreen component values to save space
2021-01-13 Lock gnd plane in place and start work on power pour
2021-01-13 backup prior to tom and carl discuss
2021-01-13 remove measures
2021-01-13 remove hidden polys from mqtr import
2021-01-13 lock mqtr layout constraint dimension lines
2021-01-13 grp mqtr ckt post revision w/ tom
2021-01-13 add DRC constraints from manufacturer, add initial layout routing for RW X and Y level shifters
2021-01-14 Replaced photodiode circuitry with updated layout and values
2021-01-14 checkpoint for moving stuf around
2021-01-14 mqtr layout checkpoint
2021-01-14 layout checkpoint
2021-01-14 preliminary layout for reaction wheel circuitry and magnetorquers
2021-01-14 more circuit laid out
2021-01-15 arranged ADCs for splitting ground plane
2021-01-15 laid out ADCs to split ground plane
2021-01-15 place temporary bom
2021-01-16 finished layout of all parts on board and most traces
2021-01-16 routed miso and mosi and slpi clocks
2021-01-16 Added reference design files for BNO055 IMU
2021-01-16 Resolve DRC clearance issues
2021-01-17 Switched analog sensor circuitry to 3v3, added connectors for actuatrors (terminal blocks), and removed unneccessary actuator footprints, format adjustments
2021-01-17 removed traces across the middle to clean up
2021-01-17 moved ADC silkscreen back onto board
2021-01-17 Found places for terminal blocks still need to look into the need for DMUX or not and switch rw x & y
2021-01-17 swapped reaction wheel drivers X & Y
2021-01-17 Replaced connector to match sensor board pinout
2021-01-18 finished traces except for power and ground plane
2021-01-18 added another wire
2021-01-19 fixed net names for sun sensors
2021-01-19 fixed design rule checks
2021-01-19 replaced 10u caps with 4.7u
2021-01-19 laid out polygons for power plane
2021-01-20 moved ADCs and X reaction wheel driver
2021-01-20 I forgot to save changes to last commit
2021-01-20 New sunsensor layout and updated sun sensor mask mount
    now all on 3v3 supply
2021-01-21 Replaced Z- Sun sensor board with copy of Z+ sun sensor board
2021-01-21 Added mounting holes for sun sensor board, added standoff mounting holes to sensor board
2021-01-21 redid traces for new positioning
2021-01-22 finished power plane
2021-01-22 split the ground plane
2021-01-25 finished top and bottom ground planes
2021-01-27 Add files via upload
    Added actuator BOM
2021-01-28 Small value updates, new titleblock, and added bom
2021-01-29 updated footprint step models
2021-01-29 sensor board updates for rev b
2021-01-29 Added boms for sun sense boards rev a
2021-01-29 updates to Z+ sun sense board for 3d models
2021-01-29 updates for 3d models for z- sun sense
2021-01-29 fixed renamed h-bridge part in schematic/board
2021-01-29 moved a bunch of digital shit around (work in progress). going to sleep now
2021-01-29 finished rearranging analog side for minimal a/d ground bridge spacing
2021-01-30 fixed silkscreen fiasco
2021-02-01 Rerouted traces no drc errors except keepout around 1 TP
2021-02-01 moved clk traces to be over ground plane
2021-02-02 Added photodiode symbols without footprint and replaced title blocks
2021-02-02 Fixed motordriver schematic for readability
2021-02-02 Formatting
2021-02-02 Added missing decoupling caps and cleared ERC on schematic
2021-02-02 rearranged terminal blocks and other minor changes
2021-02-02 few unsaved changes
2021-02-02 last commit before some fuckery
2021-02-03 Moved h-bridges and current sensing around for magnetorquer control
2021-02-03 Went ham. Changed motor driver layout.
    Bodied some beerz
2021-02-03 added some traces
2021-02-04 minor changes
2021-02-05 routed all main traces
2021-02-05 cleared drc errors ready for review
2021-02-10 Added BNO055 IMU to sensor board schematic
2021-02-10 Added new connectors for maxon motors
2021-02-11 changed reaction wheel connector routings
2021-02-12 Updated schematic fomatting and added DSS bitmap logo
2021-02-12 fixed drc errors
2021-02-12 incorporated carls changes
2021-02-12 placed logos
2021-02-12 placed our names
2021-02-14 Finalized sun sense board
2021-02-14 Minor gerber updates to copper
2021-02-14 Adding CAM outputs
2021-02-14 moved silk ref des around
2021-02-14 moved silk ref des around some more
2021-02-14 manafacturing outputs
2021-02-14 minor layout tweaks
2021-02-16 filled in ground spots and rearranged designators
2021-02-17 Updated new reaction wheel footprint, silk and 3d model
2021-02-17 Updates to layout silk/traces
2021-02-17 Slight layout tweaks
2021-02-17 Replaced jumpers with circular pads
2021-02-17 solved drc errors
2021-02-17 moved text and test point
2021-02-17 removed 90 degree trace corners
2021-02-17 Replaced TVS991AILT opa,mp schematic symbol for readability
2021-02-17 Last commit before bullshit
2021-02-17 I think i fixed it
2021-02-17 Silk & via fix
2021-02-18 another 2 mm
2021-02-18 im fckn drunk
2021-02-18 silk update for photodiode direction connection
2021-02-18 Schematic notes edit
2021-02-18 Added jumpers for selecting motor break mode
2021-02-18 Layed out brake mode select jumpers
2021-02-18 Deleted stub
2021-02-19 DONE THIS MFER
2021-02-19 mInor silk tweaks
2021-02-19 cleared drc erros
2021-02-19 changed values for resistance of sun sensor amp
2021-02-19 moved via that was covered by silk
2021-02-19 final changes before submission
2021-02-19 bom edit
2021-02-19 Added bom file and rev # to schematic
2021-02-19 Added actuator board release zip
2021-02-26 Updated git ignore for extracted release files
2021-02-26 Added X & Y sun sensor connectors to Z- Sun Sense Board
2021-02-26 Removed the godawful sun sensing circuitry
2021-02-26 Deleted extra silk
2021-02-26 Added indicator LED
2021-02-27 Sanity check
2021-02-27 Schematic Updates
2021-02-27 Added PCB flex circuits
2021-02-28 Added ltspice simulation
2021-02-28 Updated current sense circuitry
2021-02-28 Added some notes
2021-02-28 Adding spice model for tsv991ailt from stm and additional current sense models
2021-02-28 Add tsv991 spice model
2021-03-02 Fixed wrong motor connector pinout
2021-03-05 tied floating pins on Actuator Board
2021-03-05 tied floating pins on sensor board
2021-03-10 Renamed files
2021-03-10 Removed old renamed files
2021-03-10 Added 5.1M ohms to BNO055 no connect pins
2021-03-10 Added missing power supplies to magnetorquer current senses
2021-03-21 bfwebfibc
2021-03-22 Major layout changes check point
    New connectors, analog plane reshape, moved msp430
2021-03-23 Draft of Rev B done
2021-03-23 Updated sims for current sensing
2021-03-23 More board layout updates
2021-03-26 Updated motherboad layout
2021-03-30 Last commit before major layout changes on Actuator board Rev B
